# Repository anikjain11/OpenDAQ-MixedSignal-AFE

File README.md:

# OpenDAQ-AFE: Mixed-Signal Detector Readout & DAQ Pipeline

<div align="center">

</div>

---

## 🔬 Project Overview

**OpenDAQ-AFE** is an open-source, production-grade mixed-signal data acquisition (DAQ) and detector front-end architecture. Designed for high-energy physics instrumentation, this system bridges microscopic sensor physics to real-time digital signal processing.

It takes a sub-nanosecond, femtocoulomb-level current pulse generated by a particle hit on a semiconductor sensor, processes it through an ultra-low noise analog front-end (AFE), and digitizes the signal via a high-speed path. 

---

## 📐 System Architecture & Signal Chain

    [ Semiconductor Sensor (PIN Diode / 70pF) ]
                           │ 
                           ▼ (1 pC Charge Pulse, ~1ns rise)
    [ Analog Front-End (OPA656 Charge-Sensitive Preamplifier) ]
                           │ 
                           ▼ (-900mV Step, 50us Exponential Decay)
    [ Active CR-RC Pulse Shaper with PZ Cancellation ]
                           │ 
                           ▼ (~720mV Semi-Gaussian shaping peak)
    [ High-Speed Flash ADC & FPGA RTL Engine ]
                           │ 
                           ▼ (Digitized Event Frames)
    [ CERN ROOT / Python Analysis Pipeline ]

---

## 🛠️ Repository Structure

    OpenDAQ-MixedSignal-AFE/
    ├── hardware_kicad/         # 4-Layer PCB schematics, layout (.kicad_pcb), and Gerbers
    ├── simulations_spice/      # Ngspice netlists, subcircuits (.sub), and transient analysis
    │   └── CSP_FrontEnd_Simulation/
    │       ├── opa656.sub      
    │       └── README.md       # Detailed SPICE math and slew-rate bottleneck logs
    ├── results/                # Visual proof and exported documentation
    │   ├── 01_simulations/     # Python-plotted transient response graphs
    │   ├── 02_schematics/      # PDF exports of system architecture
    │   └── 03_pcb_layout/      # 2D routing and 3D board renders
    └── README.md               # Main project overview (You are here)

---

## ⚡ Sub-System 1: Analog Front-End (CSP & Shaper)

### Mathematical Foundation
The Charge-Sensitive Preamplifier (CSP) converts input charge ($Q_{in}$) into a proportional voltage step via feedback capacitance ($C_f = 1\text{ pF}$). To prevent pulse pile-up at high event rates, the 50µs CSP decay tail is compressed using an active shaping amplifier. A Pole-Zero (PZ) cancellation network perfectly counteracts the CSP's discharge time constant.

* **Active Element:** OPA656 Wideband Unity-Gain Stable JFET-Input Op-Amp
* **Detector Capacitance:** 70 pF (PIN Photodiode emulation)
* **PZ Cancellation Resistor:** $R_{pz} = 500\text{ k}\Omega$ 

> *Above: Ngspice transient analysis displaying the shaper compressing the 50µs tail into a clean ~720mV semi-Gaussian peak, triggering the 3-bit Flash ADC logic (111).*
> *Note: For a deep dive into the SPICE slew-rate limitations and behavioral modeling of the ADC, [read the Simulation Notes here](simulations_spice/Simulation_README.md).*

---

## 🖨️ Sub-System 2: Physical Hardware (4-Layer PCB)

To translate the physics into silicon, the AFE was routed onto a strictly constrained, tapeout-ready physical board.

* **Dimensions:** Ultra-compact 16.7mm x 66.5mm footprint.
* **Stackup:** 4-Layer FR-4 (Signal, Ground Plane, Power Plane, Signal) for maximum EMI shielding.
* **Mixed-Signal Isolation:** Strict physical separation between the sensitive analog RF ground planes and the high-speed digital ADC return paths to protect the microvolt-level bias currents.

### Board Renders & Routing

---

## 📜 License
This hardware design and its associated software simulations are licensed under the **CERN Open Hardware Licence v2.0 - Strongly Reciprocal (CERN-OHL-S)**. See the LICENSE file for details.

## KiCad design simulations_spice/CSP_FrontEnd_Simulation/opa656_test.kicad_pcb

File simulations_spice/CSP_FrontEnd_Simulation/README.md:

Charge-Sensitive Preamplifier (CSP) Front-End

Objective: 
Design an ultra-low bias current analog front-end to integrate a 1 pC fast current pulse (simulating a particle strike on a 70 pF PIN photodiode) into a measurable voltage step.

Architecture & Math:
Op-Amp: OPA656 (JFET input for low current noise).
Gain Stage: Feedback capacitor $C_f = 1\text{ pF}$ designed to yield a step voltage of $-1\text{ V}$ for a $1\text{ pC}$ input charge.
Discharge Path: Feedback resistor $R_f = 50\text{ M}\Omega$ placed in parallel to prevent saturation, setting a continuous discharge time constant of $\tau = 50\ \mu\text{s}$.

Analysis: 
Transient analysis confirms the theoretical derivations. The initial charge injection drives the output to approximately -900 mV. At $t = 50\ \mu\text{s}$, the signal decays to -330 mV, perfectly aligning with the $e^{-1}$ theoretical discharge curve.

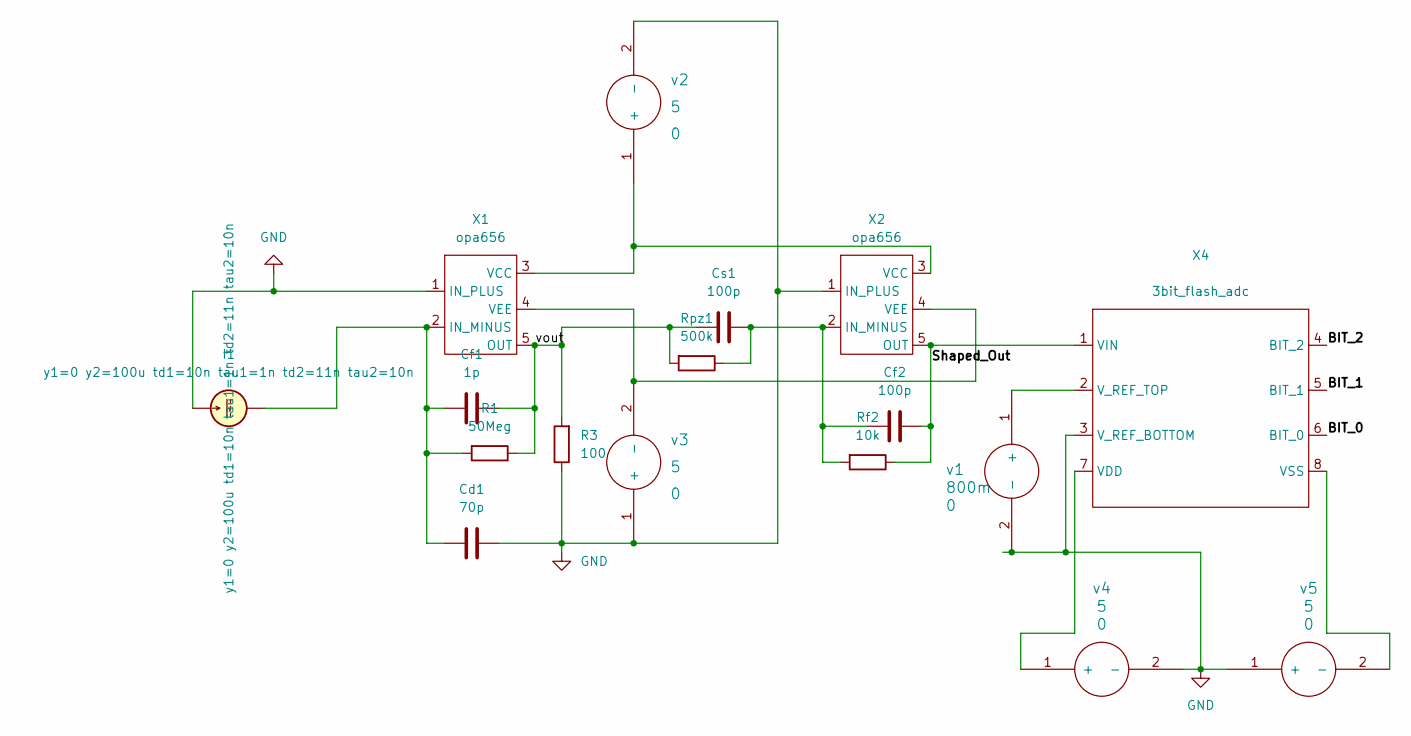
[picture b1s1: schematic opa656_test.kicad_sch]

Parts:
Cd1: 70p
Cf1: 1p
Cf2: 100p
Cs1: 100p
I1: y1=0 y2=100u td1=10n tau1=1n td2=11n tau2=10n
R1: 50Meg
R3: 100
Rf2: 10k
Rpz1: 500k
X1, X2: opa656
X4: (no value)
v1: 800m; 0
v2, v3, v4, v5: 5; 0

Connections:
/BIT_0: X4.6 (BIT_0); also elsewhere on the board
/BIT_1: X4.5 (BIT_1); also elsewhere on the board
/BIT_2: X4.4 (BIT_2); also elsewhere on the board
/Shaped_Out: Cf2.2, Rf2.1, X2.5 (OUT), X4.1 (VIN)
/vout: Cf1.2, Cs1.1, R1.1, R3.2, Rpz1.2, X1.5 (OUT)
GND: Cd1.2, I1.1, R3.1, X1.1 (IN_PLUS), X2.1 (IN_PLUS), X4.3 (V_REF_BOTTOM), v1.2 (-), v2.2 (-), v3.1 (+), v4.2 (-), v5.1 (+)
unnamed: Cd1.1, Cf1.1, I1.2, R1.2, X1.2 (IN_MINUS)
unnamed: X1.3 (VCC), X2.3 (VCC), v2.1 (+)
unnamed: X1.4 (VEE), X2.4 (VEE), v3.2 (-)
unnamed: Cf2.1, Cs1.2, Rf2.2, Rpz1.1, X2.2 (IN_MINUS)
unnamed: X4.7 (VDD), v4.1 (+)
unnamed: X4.8 (VSS), v5.2 (-)
unnamed: X4.2 (V_REF_TOP), v1.1 (+)

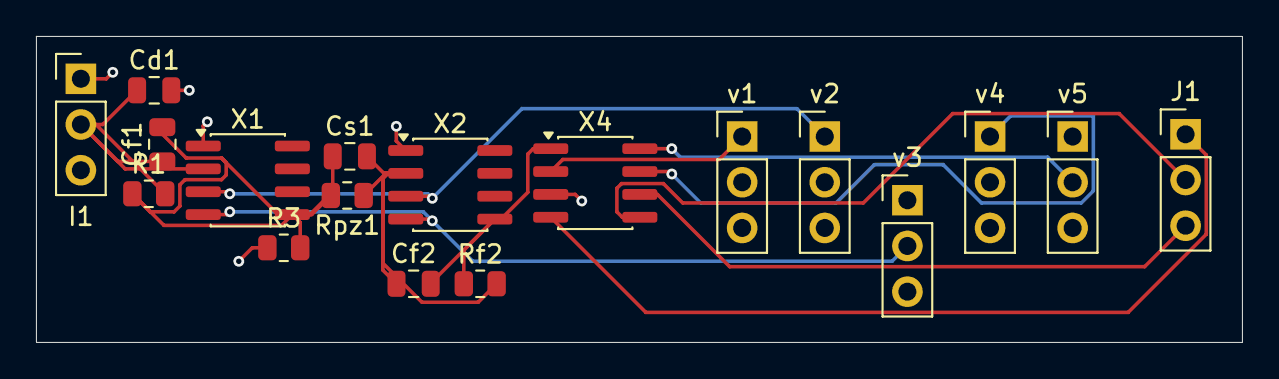
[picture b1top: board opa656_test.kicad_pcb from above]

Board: 4 copper layers, 67.0 x 17.0 mm, 18 parts (0 on the bottom side), 13 nets.

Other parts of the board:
J1: Conn_01x03; PinHeader_1x03_P2.54mm_Vertical

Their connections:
/BIT_0: J1.3; also elsewhere on the board
/BIT_1: J1.2; also elsewhere on the board
/BIT_2: J1.1; also elsewhere on the board

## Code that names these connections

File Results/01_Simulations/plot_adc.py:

import pandas as pd
import matplotlib.pyplot as plt

# 1. Load the exported KiCad CSV
df = pd.read_csv('adc_digital_out.csv', sep=';')
df.columns = df.columns.str.strip()
df = df.apply(pd.to_numeric, errors='coerce')

# Convert time to microseconds
time = df.iloc[:, 0] * 1e6  

# 2. Set up a 4-row stacked layout
fig, axs = plt.subplots(4, 1, figsize=(10, 9), sharex=True)
fig.suptitle('OpenDAQ Mixed-Signal AFE: 3-Bit Flash ADC Transient Response', fontsize=14, fontweight='bold')

# 3. Plot BIT_2 (MSB)
axs[0].plot(time, df['V(/BIT_2)'], color='blue', linewidth=2)
axs[0].set_ylabel('BIT_2\n(5V Logic)')
axs[0].set_ylim(-0.5, 5.5)
axs[0].grid(True, linestyle='--', alpha=0.6)

# 4. Plot BIT_1
axs[1].plot(time, df['V(/BIT_1)'], color='green', linewidth=2)
axs[1].set_ylabel('BIT_1\n(5V Logic)')
axs[1].set_ylim(-0.5, 5.5)
axs[1].grid(True, linestyle='--', alpha=0.6)

# 5. Plot BIT_0 (LSB)
axs[2].plot(time, df['V(/BIT_0)'], color='red', linewidth=2)
axs[2].set_ylabel('BIT_0\n(5V Logic)')
axs[2].set_ylim(-0.5, 5.5)
axs[2].grid(True, linestyle='--', alpha=0.6)

# 6. Plot the Analog Input Pulse
axs[3].plot(time, df['V(/Shaped_Out)'], color='purple', linewidth=2)
axs[3].set_ylabel('Shaped Pulse\n(V)')
axs[3].set_xlabel('Time (µs)')
axs[3].grid(True, linestyle='--', alpha=0.6)

# Save the final high-res image
plt.tight_layout()
plt.savefig('adc_publication_plot.png', dpi=300)
print("Complete 4-panel publication plot successfully saved as adc_publication_plot.png!")

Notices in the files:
README.md:
License: CERN-OHL-S
